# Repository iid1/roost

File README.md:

# roost

[Japanese README is available here](./README_ja.md)

# Overview
roost is a system designed to make a wrist-rest-integrated mouse (referred to as a "wrist mouse") practical and functional.
The wrist mouse itself is named **perch**, which serves as the core product of this repository and the origin of the entire concept.
Due to its form factor as a wrist rest, buttons cannot be practically integrated into perch, meaning a separate companion device is necessary for click and navigation operations.
The overarching ecosystem encompassing these complementary devices is named **roost**.

*(Left: sub_feeder, Right: disassembled perch)*

This repository is published in the hope of supporting and inspiring the DIY and maker activities of anyone intrigued by the concept of wrist-worn / wrist-rest pointing devices.
While provided under an open hardware license, use and modification are freely encouraged.
Please note that I am a hobbyist and not a professional in circuit design, so please feel free to improve, refine, and adapt the designs.
Issues and Pull Requests are warmly welcome!

### Acknowledgments
- In developing this hardware, the optical sensor and power circuitry are modified from the open-source hardware [**BOB-PMW3360-SUMI**](https://github.com/snize/BOB-PMW3360-SUMI) (Reference product: [PMW3360 Breakout Board SUMI](https://bulblub.booth.pm/items/6164153)) created by **Tomotsugu Kaneko ([@snize](https://github.com/snize))**. I express my sincere gratitude for making this design openly available on GitHub.
- This documentation also references and includes photos featuring [**KobitoKey (小人キー)**](https://iikagen-11.booth.pm/items/7511676) by **[@juichi50iii](https://github.com/juichi50iii)**.

---

## System Structure & Table of Contents

### Ecosystem Devices
- [**perch**](#perch): Wrist-rest optical mouse (PixArt PMW3360 + Seeed Studio XIAO BLE)
  - [Features](#features) / [Philosophy](#philosophy)
- [**sub_feeder**](#sub_feeder): Left-hand companion controller with 5 keyswitches & EC11 rotary encoder
  - [Philosophy](#philosophy-1)
- *(Upcoming)* **feeder**: Ergonomic keyboard designed specifically to complement perch

### Table of Contents
- [Overview](#overview)
- [perch](#perch)
  - [Features](#features)
  - [Philosophy](#philosophy)
- [sub_feeder](#sub_feeder)
  - [Philosophy](#philosophy-1)
- [Design & Operational Philosophy](#design--operational-philosophy)
  - [Challenges of Wrist Mice](#challenges-of-wrist-mice)
  - [How roost Solves It (perch + sub_feeder)](#how-roost-solves-it-perch--sub_feeder)
- [Directory Structure](#directory-structure)
- [Hardware Specifications & JLCPCB Manufacturing Guide](#hardware-specifications--jlcpcb-manufacturing-guide)
  - [1. perch (Wrist-Rest Mouse)](#1-perch-wrist-rest-mouse)
  - [2. sub_feeder (Left-Hand Controller)](#2-sub_feeder-left-hand-controller)
- [sub_feeder Layer Mapping](#sub_feeder-layer-mapping)
- [Automated Firmware Builds via GitHub Actions](#automated-firmware-builds-via-github-actions)
- [Flashing the Firmware](#flashing-the-firmware)
- [Notes & Tips](#notes--tips)
- [Licenses & Attribution](#licenses--attribution)
- [Changelog](#changelog)

---

# perch
A dedicated device for navigating the mouse cursor.
It is the main product of this repository.

## Features
- Operated with your wrist or the base of your palm resting naturally on top.
- Because it has no built-in click mechanism, its vertical depth is very slim, allowing it to sit right in front of your keyboard.

## Philosophy
The features above are essentially those of a conventional wrist rest (palm rest), with pointing functionality added directly into it.
This device was created to eliminate physical strain on the wrist.
While I feel it is not yet fully refined as both creator and daily user, I believe the fundamental direction of the concept is promising.

In my daily setup, I normally use a non-slip wrist rest for the keyboard and a sliding wrist rest for the mouse (as well as for trackballs).
I previously used a Keyball keyboard, but found that operating a trackball requires delicate thumb maneuvers, which surprisingly caused fatigue and strain on the wrist.
Consequently, I returned to using a dedicated pointing device, but the common dilemma often cited when transitioning to trackball keyboards remained: *"With a standard keyboard and mouse, you have to lift and move your hand away from the keyboard whenever you need to use the mouse."*

Reflecting on this hand movement, I came to believe that the primary cause of wrist strain is the subtle lifting motion required when switching your grip onto a rounded, conventional mouse.
To eliminate this, the idea was born: *Why not add mouse functionality directly to the wrist rest that my hand is already resting on?*

The name **perch** refers to a bird's resting place / branch (止まり木).
It was named in the hope that users can operate the pointer effortlessly while resting their hands.
(Initially, I considered naming the wrist mouse *tomariGi* and the keyboard *naSashi* [菜差し, a Japanese feeder tool used to offer greens to caged birds]. However, between a perch and a green-holder, the perch is physically larger, which inverted the actual size ratio between the wrist mouse and the keyboard in this repository. Therefore, the keyboard was designated as *feeder* [餌台]. Viewing your hands as little birds pecking at the keyboard also felt fitting and charming.)

# sub_feeder
A companion device responsible for mouse clicks, wheel scrolling, and side buttons.
When perch is used with the right hand, sub_feeder is placed on the left side.
Because a wrist mouse is not grasped between your fingers, it naturally moves slightly while typing.
Furthermore, unlike a standard mouse, you cannot simply lift it slightly off the desk to reposition your hand in the air during long-distance cursor traversal without moving the pointer.
To address this, sub_feeder incorporates toggle and hold keys to dynamically enable and disable pointing output.

## Philosophy
sub_feeder is an interim stepping stone until a dedicated keyboard (*feeder*) optimized for perch is created.
To be frank, it has its inconveniences: while right-hand travel is minimized, left-hand travel increases to reach this companion device.
If you already have a ZMK-compatible programmable keyboard, assigning mouse clicks to keys on that keyboard is much more recommended. (Since feeder is not yet complete, I personally use perch paired with **KobitoKey** by [@juichi50iii](https://github.com/juichi50iii) available on [BOOTH](https://iikagen-11.booth.pm/items/7511676), running custom ZMK firmware from [KobitoKey_QWERTY_iid1](https://github.com/iid1/KobitoKey_QWERTY_iid1). Honestly, the KobitoKey setup feels so comfortable that the completion of feeder is somewhat in jeopardy—having both a trackball and perch side-by-side works surprisingly well).
Because trackball-equipped keyboards already integrate mouse actions into key bindings, pairing perch with an existing split keyboard delivers a very similar, unified experience.

*(Top: KobitoKey, Bottom: perch)*

---

## Design & Operational Philosophy

### Challenges of Wrist Mice
A wrist mouse placed directly in front of the keyboard minimizes hand movement, but conventional implementations suffer from a critical flaw: **the sensor detects subtle wrist shifts during typing, causing unintended cursor drifting**.

### How roost Solves It (perch + sub_feeder)
In roost, we leverage ZMK Firmware's `input-processor` engine to adopt the philosophy of **"activating the pointer only when needed"** and **"instantly converting wrist movement into scrolling"**:

1. **Pointer Inactive by Default (Zero Drift)**
   - In Layer 0 (default), pointer delta scaling is set to **0x (disabled)**. No matter how much your wrists shift during typing, the cursor remains completely locked in place.
2. **Intuitive Mouse Activation (Hold & Toggle)**
   - **Momentary Hold**: Holding `SW4` on sub_feeder immediately activates cursor movement (1x scale) for quick pointing gestures.
   - **Continuous Navigation**: Tapping `SW6` toggles Mouse Mode ON (Layer 2). You can point naturally with perch on your right wrist while executing Left Click (`SW2`) and Right Click (`SW3`) with your left hand.
3. **Wrist-Driven Smooth Scrolling**
   - Holding `SW6` for >500ms transitions into Scroll Mode (Layer 3).
   - Wrist movements on perch are dynamically converted into smooth 2-axis scrolling (with Y-axis inversion and fine 1/8 scaling).
4. **Zooming & Multi-Host Switching**
   - Rotating the EC11 rotary encoder zooms in/out (`Ctrl + +` / `Ctrl + -`).
   - Long-pressing the encoder push switch switches to Layer 1 for Bluetooth host switching (up to 3 paired computers), mute, and volume adjustments.

---

## Directory Structure

```text
roost/
|-- .github/
|   `-- workflows/
|       `-- build.yml               # GitHub Actions automated firmware build workflow
|-- build.yaml                      # ZMK build matrix (perch / sub_feeder)
|-- config/
|   |-- west.yml                    # PMW3360 optical sensor driver manifest
|   `-- boards/shields/             # ZMK shield definitions
|-- perch/                          # [Wrist-Rest Optical Mouse] (formerly wrist_mouse)
|   |-- circuit/                    # Schematics, PCB layout & JLCPCB manufacturing files
|   |   |-- kicad/                  # KiCad design files (.kicad_sch, .kicad_pcb)
|   |   |-- gerber/                 # JLCPCB Gerber production zip
|   |   `-- jlcpcb_smt/             # JLCPCB SMT assembly BOM & CPL CSV files
|   |-- 3dModel/                    # 3D enclosure CAD models
|   |   |-- stl/                    # STL files for 3D printing
|   |   `-- step/                   # STEP & 3MF assembly models
|   `-- firmware/                   # ZMK firmware
|       |-- prebuilt/               # Ready-to-flash .uf2 firmware binaries
|       `-- shield/                 # ZMK shield configuration & overlay
|-- sub_feeder/                     # [Left Macro Controller] (formerly left_device)
|   |-- circuit/                    # Schematics & PCB layout
|   |   |-- kicad/                  # KiCad design files (.kicad_sch, .kicad_pcb, .dxf)
|   |   |-- gerber/                 # JLCPCB Gerber production zip
|   |   `-- README.md               # Component Bill of Materials (BOM)
|   |-- 3dModel/                    # 3D enclosure CAD models
|   |   `-- step/                   # STEP & F3D CAD models
|   `-- firmware/                   # ZMK firmware
|       |-- prebuilt/               # Ready-to-flash .uf2 firmware binaries
|       `-- shield/                 # ZMK keymap & overlay definitions
|-- README.md                       # English documentation (this file)
|-- README_ja.md                    # Japanese documentation
|-- LICENSE                         # CERN-OHL-P v2 License
`-- .gitignore
```

---

## Hardware Specifications & JLCPCB Manufacturing Guide

### 1. perch (Wrist-Rest Mouse)
- **Microcontroller**: Seeed Studio XIAO BLE nRF52840 (`seeeduino_xiao_ble`)
- **Optical Sensor**: PixArt PMW3360 (`PMW3360DM-T2QU`) with dedicated lens
- **LDO**: TLV70019 (1.9V output)
- **JLCPCB Order Process**:
  1. Upload `perch/circuit/gerber/wrist_mouse.zip` to the JLCPCB PCB order page.
  2. Select 2-layer, **1.6mm thickness** (recommended) or 1.2mm.
  3. Turn ON **PCB Assembly (SMT)** and select files from `perch/circuit/jlcpcb_smt/`:
     - **BOM**: `wrist_mouse_bom.csv`
     - **CPL**: `wrist_mouse_cpl.csv`
  4. SMT assembly automatically mounts chip capacitors, resistors, and the 1.9V LDO regulator.
  5. Hand-solder parts: PMW3360 sensor IC, Seeed Studio XIAO BLE, and 3.7V LiPo battery.

### 2. sub_feeder (Left-Hand Controller)
- **Microcontroller**: Seeed Studio XIAO BLE nRF52840
- **Switches**: Kailh Choc V1 / V2 low-profile switches x5 (hotswap sockets supported)
- **Encoder**: EC11-compatible rotary encoder with push button x1
- **JLCPCB Order Process**:
  1. Upload `sub_feeder/circuit/gerber/left_device.zip` to JLCPCB.
  2. Specifications: 2-layer, 1.6mm thickness, solder mask color of choice (black, white, green, etc.).
  3. Hand-solder parts: Kailh Choc sockets x5, EC11 rotary encoder x1, XIAO BLE x1, and battery connector.

---

## sub_feeder Layer Mapping

| Layer | SW2 (D0) | SW3 (D1) | SW4 (D2) | SW5 (D3) | SW6 (D4) | SW1 (ENC_SW) | Encoder Rotation |
| :--- | :--- | :--- | :--- | :--- | :--- | :--- | :--- |
| **0: Default** | Left Click | Right Click | Japanese (Hold: Mouse ON) | English (LANG2) | Tap: Mouse Toggle<br>Hold 0.5s: Scroll | Hold: Layer 1 | Zoom In/Out (`Ctrl +-`) |
| **1: BT / Media** | Clear BLE Profile | Host 1 (BT 0) | Host 2 (BT 1) | Host 3 (BT 2) | Mute | (Held) | Volume Up / Down |
| **2: Mouse ON** | Left Click | Right Click | Japanese (Hold: Keep ON) | English | Tap: Mouse OFF<br>Hold 0.5s: Scroll | Layer 1 | Zoom In/Out (`Ctrl +-`) |
| **3: Scroll Mode** | Left Click | Right Click | Middle Click (`MCLK`) | Browser Back (`MB4`) | (Held) | Layer 1 | Zoom In/Out (`Ctrl +-`) |

- **Combos**:
  - `SW6 + SW5`: Browser Back (`MB4`)
  - `SW6 + SW4`: Middle Click (`MCLK`)

---

## Automated Firmware Builds via GitHub Actions

This repository is configured out of the box to compile firmware in the cloud:

1. Create a repository on GitHub (e.g. `roost`).
2. Push this folder:
   ```bash
   git init
   git add .
   git commit -m "feat: initial commit of roost"
   git branch -M main
   git remote add origin https://github.com/iid1/roost.git
   git push -u origin main
   ```
3. Visit the **Actions** tab on your GitHub repository. The build will run automatically in 2-3 minutes.
4. Download the `firmware.zip` artifact containing the compiled `.uf2` files.

---

## Flashing the Firmware

1. Connect Seeed Studio XIAO BLE to your computer via USB-C.
2. Quickly double-press the physical **Reset button** on the XIAO board.
3. A mass storage device (`XIAO-SENSE` or `XIAO-nRF`) will appear on your desktop.
4. Drag and drop the corresponding `.uf2` file:
   - For sub_feeder: `left_device-xiao_ble__zmk-zmk.uf2` (shield name: `left_device`)
   - For perch: `wrist_mouse-xiao_ble__zmk-zmk.uf2` (shield name: `wrist_mouse`)
5. The device will automatically reboot with the new firmware.

*(Note: If BLE pairing fails or needs a clean reset, flash `settings_reset-xiao_ble__zmk-zmk.uf2` once to both devices).*

---

## Notes & Tips
I apply mouse skates (dots/feet) to the bottom of perch for smooth gliding.
I personally use [WALLHACK Skates Dots](https://wallhack.com/products/skates-dots) (they provide great glide, although they are a bit pricey).

---

## Licenses & Attribution

### License
This project (including both original and modified hardware designs, circuits, 3D models, and documentation) is licensed under the **[CERN Open Hardware Licence Version 2 - Permissive (CERN-OHL-P v2)](LICENSE)**.

### Hardware Attribution & Derived Circuitry (BOB-PMW3360-SUMI)
The optical sensor interface and 1.9V power supply circuitry of **perch** are modified from and based on the open-source hardware project [**BOB-PMW3360-SUMI**](https://github.com/snize/BOB-PMW3360-SUMI) (Reference: [PMW3360 Breakout Board SUMI](https://bulblub.booth.pm/items/6164153)) created by **Tomotsugu Kaneko ([@snize](https://github.com/snize))**, licensed under the **[CERN OHL-P v2](https://spdx.org/licenses/CERN-OHL-P-2.0.html)**.

#### Specific Parts in perch Derived from SUMI:
The following schematic components and footprint definitions in `perch/circuit/kicad/wrist_mouse.kicad_sch` originate from BOB-PMW3360-SUMI:

| Circuit Block | Component Reference | Part / Value | Function in SUMI Design |
| :--- | :--- | :--- | :--- |
| **Sensor circuitry** | `U3` | `PMW3360DM-T2QU` | PixArt PMW3360 optical sensor IC |
| **Sensor circuitry** | `C1`, `C4` | `0.1uF` | Decoupling capacitors for PMW3360 |
| **Sensor circuitry** | `R1`, `R3` | `10k` | Pull-up resistors for Reset / NCS |
| **Sensor circuitry** | `R2` | `39R` | LED current-limiting resistor (39 ohm) |
| **1.9V Power supply** | `U2` | `TLV70019DDCR` | 1.9V LDO regulator (SOT-23-5) powering PMW3360 |
| **1.9V Power supply** | `C2` | `1uF` | Input capacitor for TLV70019 |
| **1.9V Power supply** | `C3` | `4.7uF/10V` | Output capacitor for TLV70019 |
| **KiCad Library** | Symbol / Footprint | `sumi-symbols:PMW3360DM-T2QU`<br>`sumi-footprints:PMW3360DM-T2QU` | Symbol and footprint definitions by snize |

#### Modifications Made in perch:
1. **Integrated All-in-One Design**: While BOB-PMW3360-SUMI is a standalone breakout board connected via pin headers, perch directly integrates this sensor and 1.9V LDO circuitry onto a unified mainboard alongside Seeed Studio XIAO BLE nRF52840, LiPo battery management, and custom power switching.
2. **Custom PCB Form Factor**: PCB layout and trace routing were redesigned from scratch to fit the slim wrist-rest enclosure and position the optical sensor at the ideal ergonomic contact point.

---

## Changelog

| Version | Date | Description |
| :--- | :--- | :--- |
| **v1.0** | 2026-11-03 | Initial release of roost / perch / sub_feeder documentation |

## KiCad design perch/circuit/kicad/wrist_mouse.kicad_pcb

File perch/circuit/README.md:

# perch - Circuit (基板・回路データ)

リストレスト型マウス（perch）の JLCPCB 発注用 Gerber データ、KiCad 設計ファイル、および SMT 実装用ファイル群です。

## ファイル構成
- `gerber/`: JLCPCB 発注用 Gerber ファイル一式
  - `wrist_mouse.zip`: JLCPCB にそのままアップロードする zip ファイル
- `jlcpcb_smt/`: JLCPCB SMT 部品実装用
  - `wrist_mouse_bom.csv`: 部品表 (BOM)
  - `wrist_mouse_cpl.csv`: 部品座標・実装角度表 (Pick & Place / CPL)
- `kicad/`: KiCad 設計データ (`wrist_mouse.kicad_sch`, `wrist_mouse.kicad_pcb` など)

## JLCPCB 発注手順
1. JLCPCB の PCB 発注画面で `gerber/wrist_mouse.zip` をアップロードします。
2. 仕様: 2層, 厚み **1.6mm** (推奨) または 1.2mm。
3. **PCB Assembly (SMT)** を選択し、表面 (Top Layer) 実装を指定します。
4. `jlcpcb_smt/wrist_mouse_bom.csv` と `wrist_mouse_cpl.csv` をアップロードします。
5. 以下のチップ部品が自動実装されます：
   - C1, C4: 0.1uF 0805
   - C2: 1uF 0805
   - C3: 4.7uF 0805
   - R1, R3: 10k 0805
   - R2: 39Ω 0805
   - U2: TLV70019DDCR (1.9V LDO)
6. 手半田パーツ：
   - PixArt PMW3360 センサー & レンズ
   - Seeed Studio XIAO BLE
   - リチウムポリマーバッテリー (3.7V)

## ライセンス・著作権表示 (BOB-PMW3360-SUMI)
本基板の PMW3360 センサー回路および 1.9V LDO 電源回路（U2, U3, C1〜C4, R1〜R3）は、Tomotsugu Kaneko (@snize) 氏によるオープンソースハードウェア [BOB-PMW3360-SUMI](https://github.com/snize/BOB-PMW3360-SUMI)（CERN-OHL-P v2 ライセンス）を元に改変・統合した設計です。
詳細はルートの [README_ja.md](../../README_ja.md) および [LICENSE](../../LICENSE) をご覧ください。

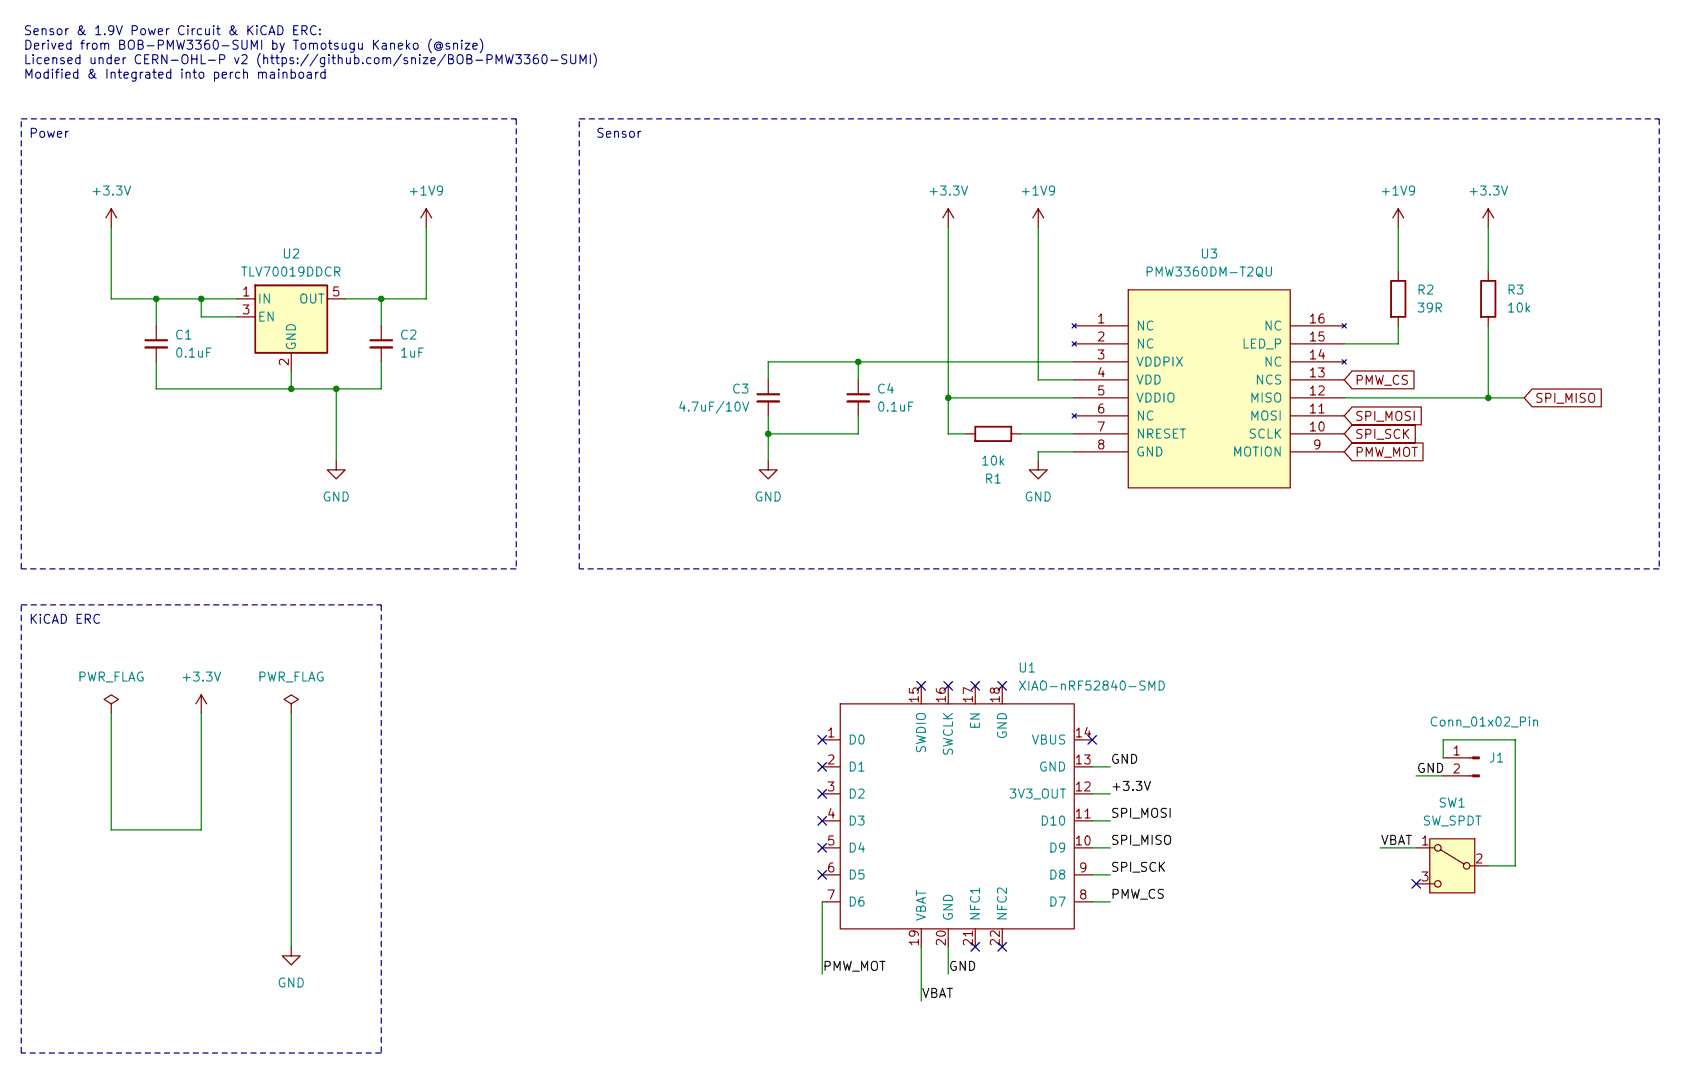
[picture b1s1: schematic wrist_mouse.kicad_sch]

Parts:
C1, C4: 0.1uF; C_0805_2012Metric_Pad1.18x1.45mm_HandSolder
C2: 1uF; C_0805_2012Metric_Pad1.18x1.45mm_HandSolder
C3: 4.7uF/10V; C_0805_2012Metric_Pad1.18x1.45mm_HandSolder
J1: Conn_01x02_Pin; PinHeader_1x02_P2.54mm_Vertical
R1, R3: 10k; R_0805_2012Metric_Pad1.20x1.40mm_HandSolder
R2: 39R; R_0805_2012Metric_Pad1.20x1.40mm_HandSolder
SW1: SW_SPDT; SW_SPDT_PCM12
U1: XIAO-nRF52840-SMD
U2: TLV70019DDCR; SOT-23-5_HandSoldering
U3: PMW3360DM-T2QU

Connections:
+1V9: C2.1, R2.1, U2.5 (OUT), U3.4 (VDD)
+3.3V: C1.1, R1.2, R3.1, U1.12 (3V3_OUT), U2.1 (IN), U2.3 (EN), U3.5 (VDDIO)
/VBAT: SW1.1 (A), U1.19 (VBAT)
GND: C1.2, C2.2, C3.2, C4.2, J1.2, U1.13 (GND), U1.20 (GND), U2.2 (GND), U3.8 (GND)
unnamed: J1.1, SW1.2 (B)
unnamed: R2.2, U3.15 (LED_P)
unnamed: R1.1, U3.7 (NRESET)
unnamed: C3.1, C4.1, U3.3 (VDDPIX)
PMW_CS: U1.8 (D7), U3.13 (NCS)
PMW_MOT: U1.7 (D6), U3.9 (MOTION)
SPI_MISO: R3.2, U1.10 (D9), U3.12 (MISO)
SPI_MOSI: U1.11 (D10), U3.11 (MOSI)
SPI_SCK: U1.9 (D8), U3.10 (SCLK)

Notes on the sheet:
Sensor
Sensor & 1.9V Power Circuit & KiCAD ERC: Derived from BOB-PMW3360-SUMI by Tomotsugu Kaneko (@snize) Licensed under CERN-OHL-P v2 (https://github.com/snize/BOB-PMW3360-SUMI) Modified & Integrated into perch mainboard
KiCAD ERC
Power

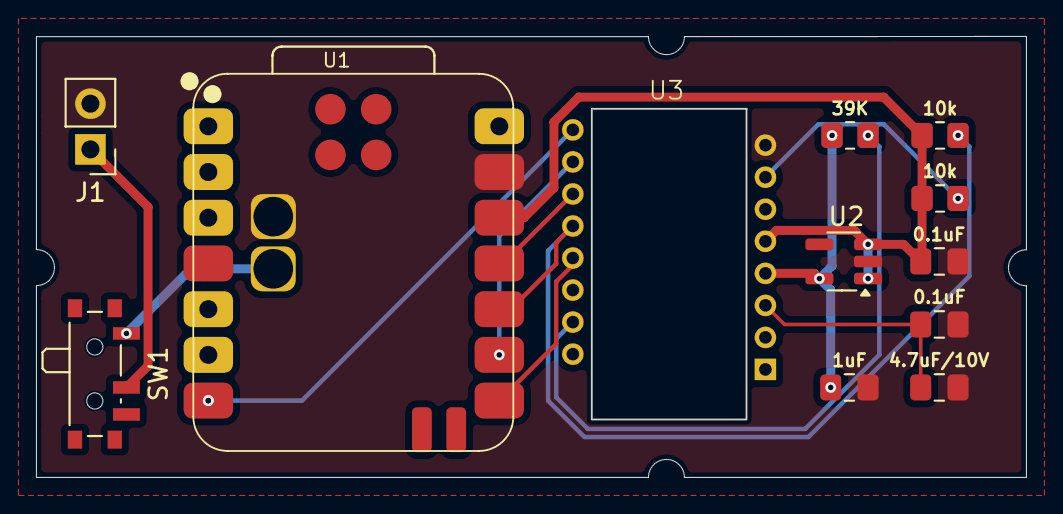
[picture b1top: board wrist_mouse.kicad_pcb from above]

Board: 2 copper layers, 55.0 x 24.5 mm, 12 parts (0 on the bottom side), 13 nets.

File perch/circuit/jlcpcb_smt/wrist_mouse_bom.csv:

Designator,Comment,Footprint,LCSC Part #
C1,0.1uF,C_0805,C49970
C2,1uF,C_0805,C28323
C3,4.7uF/10V,C_0805,C15850
C4,0.1uF,C_0805,C49970
R1,10k,R_0805,C17414
R2,39R,R_0805,C17631
R3,10k,R_0805,C17414
U2,TLV70019DDCR,SOT-23-5,C2862411

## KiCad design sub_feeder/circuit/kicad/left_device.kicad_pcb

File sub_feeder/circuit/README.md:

# Sub Feeder - Circuit (基板・回路データ)

左手コントローラー（Sub Feeder）の KiCad 設計データ、JLCPCB 発注用 Gerber データです。

## フォルダ構成
- `gerber/`: JLCPCB 発注用 Gerber ファイル一式
  - `left_device.zip`: JLCPCB にそのままアップロードする zip ファイル
- `kicad/`: KiCad 設計データ (`left_device.kicad_sch`, `left_device.kicad_pcb`, `left_device.dxf` など)

## 部品構成 (BOM)
- **マイコン**: Seeed Studio XIAO BLE nRF52840 × 1
- **キースイッチ**: Kailh Choc V1 / V2 ロープロファイルスイッチ × 5
- **ホットスワップソケット**: Kailh Choc ソケット × 5
- **ロータリーエンコーダー**: EC11互換ロータリーエンコーダー (プッシュスイッチ付き) × 1
- **電源**: 3.7V リチウムポリマーバッテリー (JST-PH または直はんだ)

## JLCPCB 発注手順
1. `gerber/left_device.zip` を JLCPCB の PCB 発注画面にアップロードします。
2. 仕様: 2層, 1.6mm 厚, お好みの色（黒、紫など）。
3. 本基板はスルーホール・ソケット部品で構成されているため、SMT実装なし（PCB製造のみ）で安価に発注可能です。

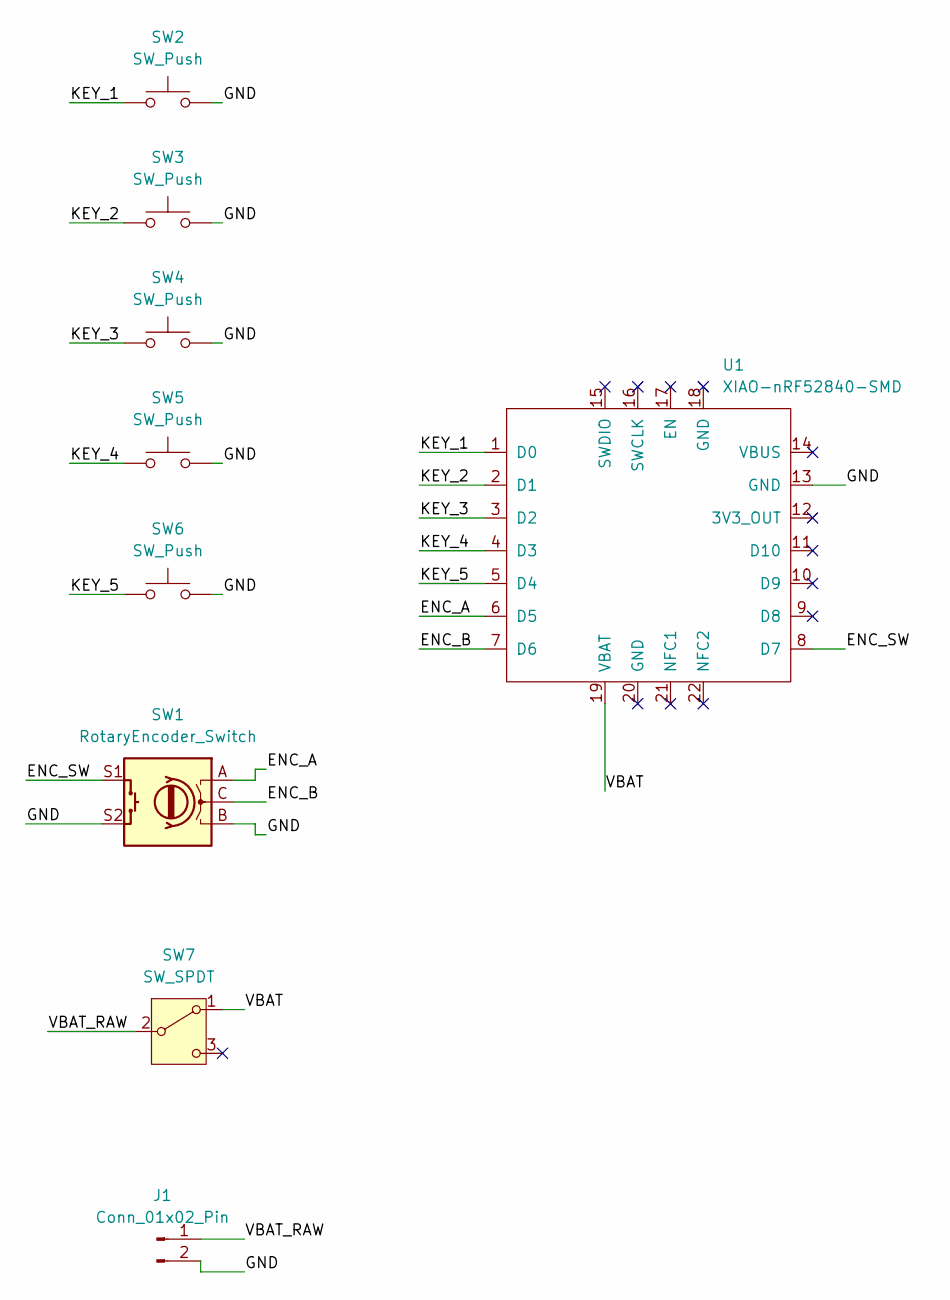
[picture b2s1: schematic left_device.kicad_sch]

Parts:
J1: Conn_01x02_Pin; PinHeader_1x02_P2.54mm_Vertical
SW1: RotaryEncoder_Switch; RotaryEncoder_Alps_EC12E-Switch_Vertical_H20mm
SW2, SW3, SW4, SW5, SW6: SW_Push; SW_Kailh_Choc_V1V2_HotSwap_Hybrid
SW7: SW_SPDT; SW_SPDT_PCM12
U1: XIAO-nRF52840-SMD

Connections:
/ENC_A: SW1.A, U1.6 (D5)
/ENC_B: SW1.C, U1.7 (D6)
/ENC_SW: SW1.S1, U1.8 (D7)
/GND: J1.2, SW1.B, SW1.S2, SW2.2, SW3.2, SW4.2, SW5.2, SW6.2, U1.13 (GND)
/KEY_1: SW2.1, U1.1 (D0)
/KEY_2: SW3.1, U1.2 (D1)
/KEY_3: SW4.1, U1.3 (D2)
/KEY_4: SW5.1, U1.4 (D3)
/KEY_5: SW6.1, U1.5 (D4)
/VBAT: SW7.1 (A), U1.19 (VBAT)
/VBAT_RAW: J1.1, SW7.2 (B)

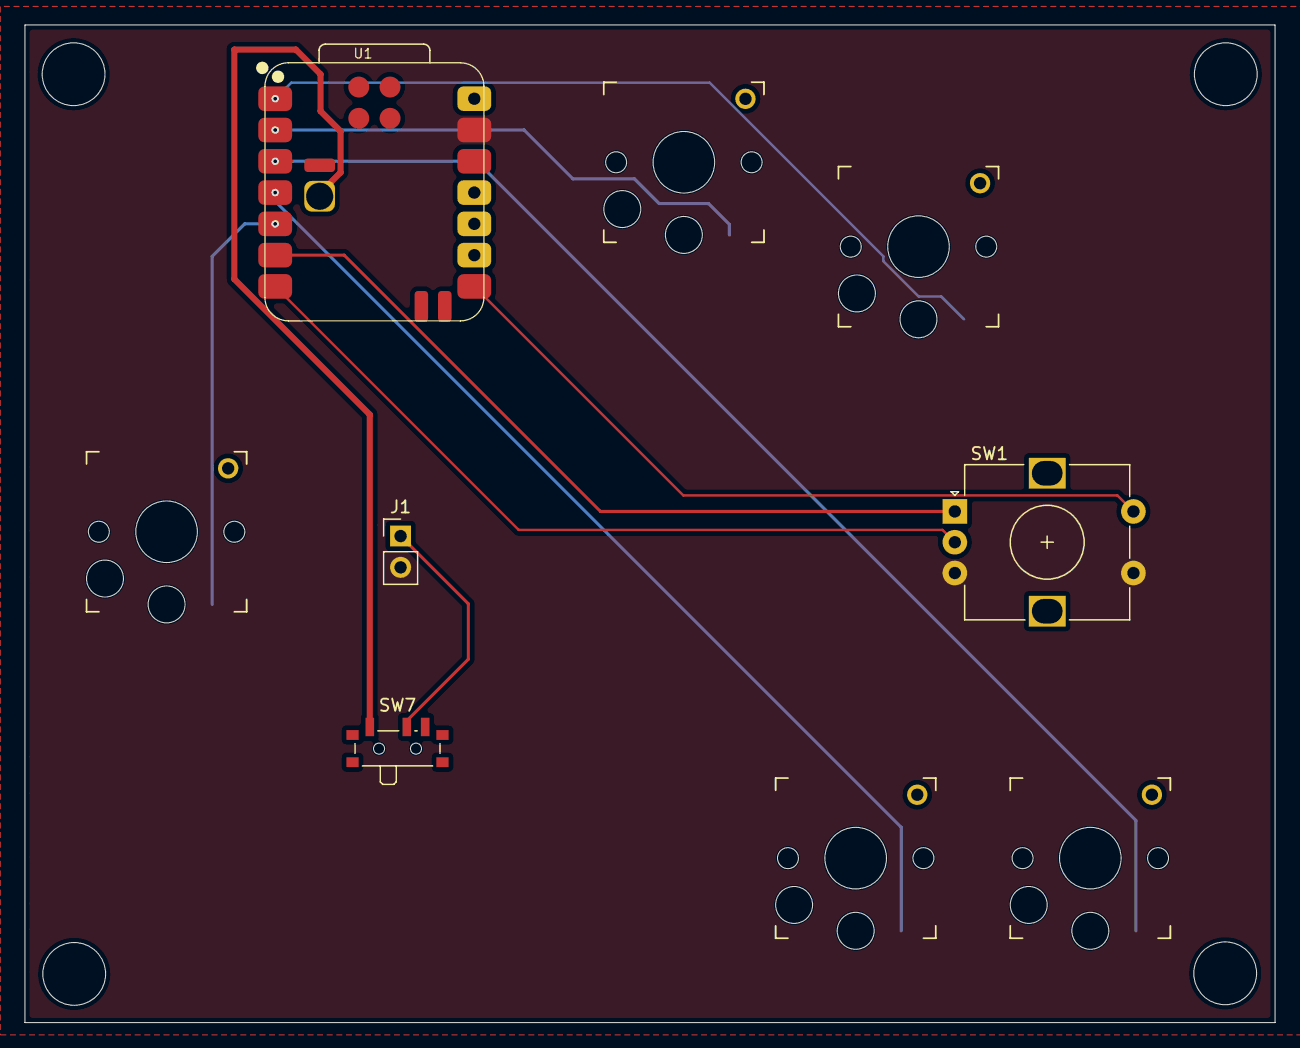
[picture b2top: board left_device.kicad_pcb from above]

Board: 2 copper layers, 101.5 x 81.0 mm, 9 parts (0 on the bottom side), 11 nets.

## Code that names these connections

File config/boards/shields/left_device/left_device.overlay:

/*
 * Copyright (c) 2026 The ZMK Contributors
 * SPDX-License-Identifier: MIT
 */

#include <dt-bindings/zmk/matrix_transform.h>

/ {
    chosen {
        zmk,kscan = &kscan0;
        zmk,matrix-transform = &default_transform;
    };

    default_transform: keymap_transform_0 {
        compatible = "zmk,matrix-transform";
        columns = <6>;
        rows = <1>;
        map = <
            RC(0,0) RC(0,1) RC(0,2) RC(0,3) RC(0,4) RC(0,5)
        >;
    };

    kscan0: kscan {
        compatible = "zmk,kscan-gpio-direct";
        input-gpios
            = <&xiao_d 0 (GPIO_ACTIVE_LOW | GPIO_PULL_UP)> // SW2 (KEY_1)
            , <&xiao_d 1 (GPIO_ACTIVE_LOW | GPIO_PULL_UP)> // SW3 (KEY_2)
            , <&xiao_d 2 (GPIO_ACTIVE_LOW | GPIO_PULL_UP)> // SW4 (KEY_3)
            , <&xiao_d 3 (GPIO_ACTIVE_LOW | GPIO_PULL_UP)> // SW5 (KEY_4)
            , <&xiao_d 4 (GPIO_ACTIVE_LOW | GPIO_PULL_UP)> // SW6 (KEY_5)
            , <&xiao_d 7 (GPIO_ACTIVE_LOW | GPIO_PULL_UP)> // SW1 (ENC_SW)
            ;
    };

    left_encoder: encoder_left {
        compatible = "alps,ec11";
        a-gpios = <&xiao_d 5 (GPIO_ACTIVE_HIGH | GPIO_PULL_UP)>;
        b-gpios = <&xiao_d 6 (GPIO_ACTIVE_HIGH | GPIO_PULL_UP)>;
        steps = <80>;
        status = "okay";
    };

    sensors: sensors {
        compatible = "zmk,keymap-sensors";
        sensors = <&left_encoder>;
        triggers-per-rotation = <80>;
    };

    split_inputs {
        #address-cells = <1>;
        #size-cells = <0>;

        pmw3360_split: pmw3360_split@0 {
            compatible = "zmk,input-split";
            reg = <0>;
        };
    };

    pmw3360_listener: pmw3360_listener {
        compatible = "zmk,input-listener";
        device = <&pmw3360_split>;
    };
};

/* Disable UART0 so D6 (TX) and D7 (RX) can be used as GPIO pins (Encoder B and Push switch) */
&uart0 {
    status = "disabled";
};

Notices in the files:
README.md:
License: CERN-OHL-P-2.0
